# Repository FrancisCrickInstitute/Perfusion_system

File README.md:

# Perfusion_system

This system is composed by a 3D printed lid for 35 mm petri dishes, two peristaltic pumps and a control board which controls the flow rate of both pumps simultaneously.

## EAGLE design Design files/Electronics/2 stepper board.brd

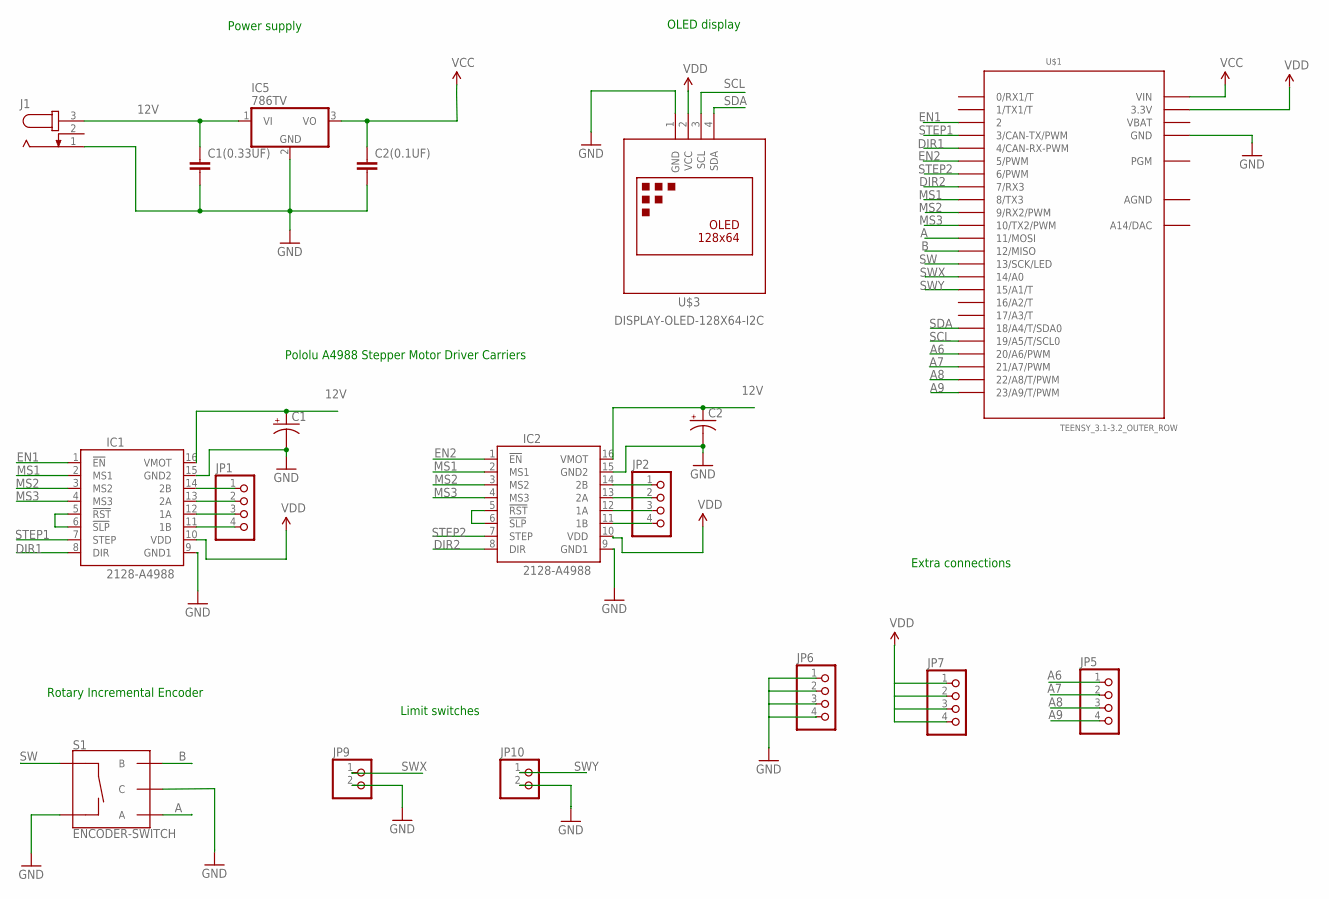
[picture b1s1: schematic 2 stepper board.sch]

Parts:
C1, C2: CPOL-USE5-5; E5-5
C1(0.33UF): C2.5/4; C2.5-4
C2(0.1UF): C2.5/2; C2.5-2
IC1, IC2: 2128-A4988; A4988
IC5: 786TV; TO220V
J1: JACK-PLUG0; SPC4077
JP1, JP2, JP5, JP6, JP7: PINHD-1X4; 1X04
JP9, JP10: PINHD-1X2; 1X02
S1: ENCODER-SWITCH; ROTARY_ENC_PLAIN
U$1: TEENSY_3.1-3.2_OUTER_ROW; TEENSY_3.0-3.2&LC_OUTER_ROW
U$3: DISPLAY-OLED-128X64-I2C

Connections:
12V: C1.+, C1(0.33UF).1, C2.+, IC1.16 (VMOT), IC2.16 (VMOT), IC5.1 (VI), J1.3
A: S1.A, U$1.11 (11/MOSI)
A6: JP5.1, U$1.20/A6 (20/A6/PWM)
A7: JP5.2, U$1.21/A7 (21/A7/PWM)
A8: JP5.3, U$1.22/A8 (22/A8/T/PWM)
A9: JP5.4, U$1.23/A9 (23/A9/T/PWM)
AGND: U$1.AGND
B: S1.B, U$1.12 (12/MISO)
DIR1: IC1.8 (DIR), U$1.4 (4/CAN-RX-PWM)
DIR2: IC2.8 (DIR), U$1.7 (7/RX3)
EN1: IC1.1 (!EN), U$1.2
EN2: IC2.1 (!EN), U$1.5 (5/PWM)
GND: C1.-, C1(0.33UF).2, C2.-, C2(0.1UF).2, IC1.9 (GND1), IC1.15 (GND2), IC2.9 (GND1), IC2.15 (GND2), IC5.2 (GND), J1.1, JP6.1, JP6.2, JP6.3, JP6.4, JP9.2, JP10.2, S1.C, S1.SW-, U$1.GND, U$1.GND1 (GND), U$3.1 (GND)
MS1: IC1.2 (MS1), IC2.2 (MS1), U$1.8 (8/TX3)
MS2: IC1.3 (MS2), IC2.3 (MS2), U$1.9 (9/RX2/PWM)
MS3: IC1.4 (MS3), IC2.4 (MS3), U$1.10 (10/TX2/PWM)
unnamed: IC1.14 (2B), JP1.1
unnamed: IC1.13 (2A), JP1.2
unnamed: IC1.12 (1A), JP1.3
unnamed: IC1.11 (1B), JP1.4
unnamed: IC2.14 (2B), JP2.1
unnamed: IC2.13 (2A), JP2.2
unnamed: IC2.12 (1A), JP2.3
unnamed: IC2.11 (1B), JP2.4
unnamed: IC2.5 (!RST), IC2.6 (!SLP)
unnamed: IC1.5 (!RST), IC1.6 (!SLP)
SCL: U$1.19/A5 (19/A5/T/SCL0), U$3.3 (SCL)
SDA: U$1.18/A4 (18/A4/T/SDA0), U$3.4 (SDA)
STEP1: IC1.7 (STEP), U$1.3 (3/CAN-TX/PWM)
STEP2: IC2.7 (STEP), U$1.6 (6/PWM)
SW: S1.SW+, U$1.13 (13/SCK/LED)
SWX: JP9.1, U$1.14/A0
SWY: JP10.1, U$1.15/A1 (15/A1/T)
VBAT: U$1.VBAT
VCC: C2(0.1UF).1, IC5.3 (VO), U$1.VIN
VDD: IC1.10 (VDD), IC2.10 (VDD), JP7.1, JP7.2, JP7.3, JP7.4, U$1.3.3V, U$1.3.3V1 (3.3V), U$3.2 (VCC)

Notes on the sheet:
Pololu A4988 Stepper Motor Driver Carriers
OLED display
Power supply
Rotary Incremental Encoder
Extra connections
Limit switches

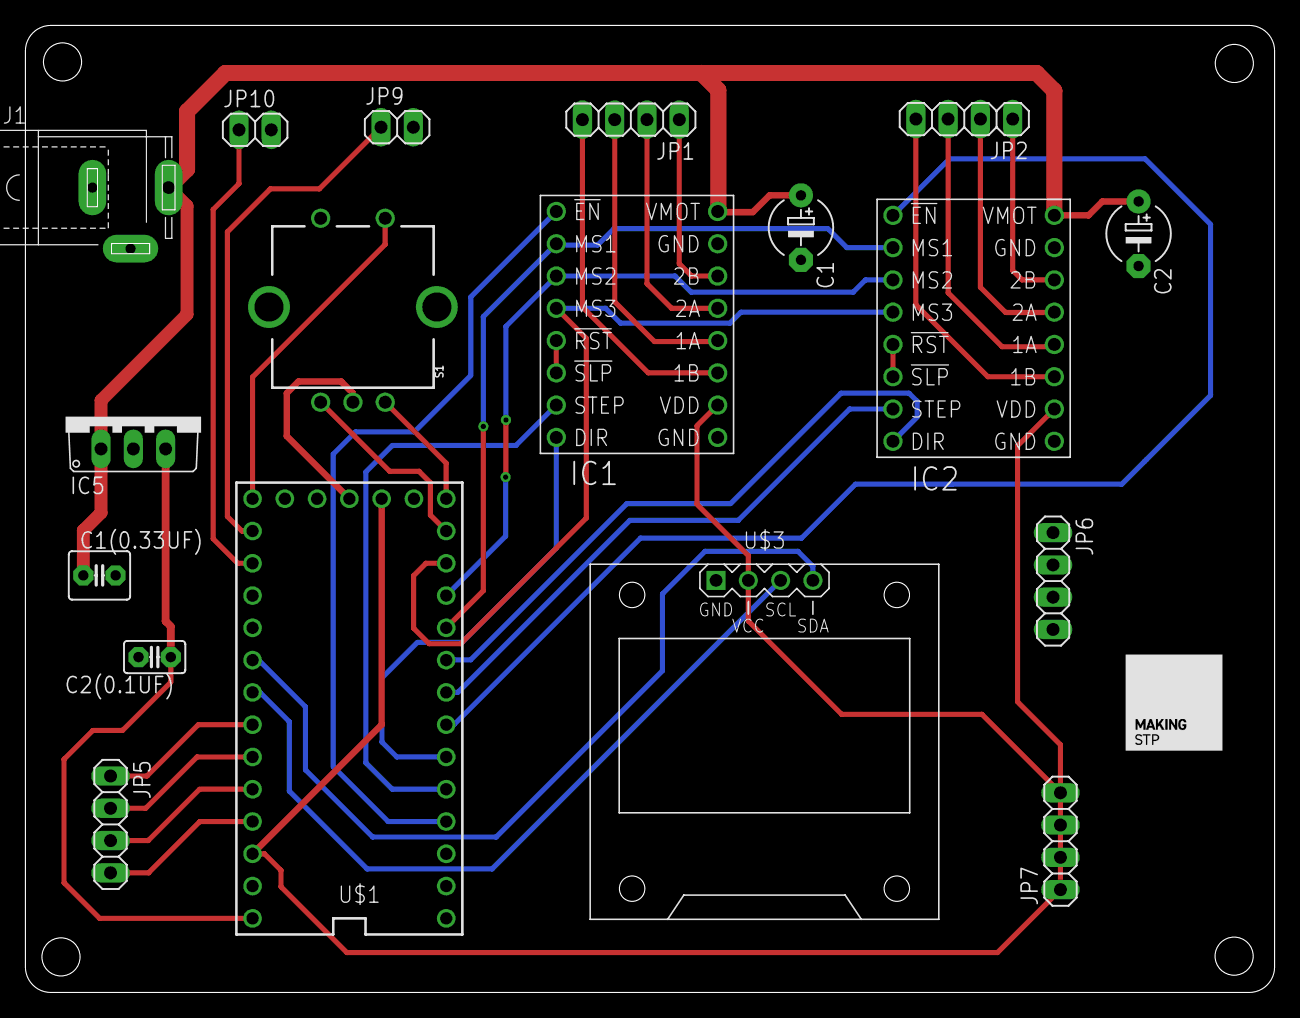
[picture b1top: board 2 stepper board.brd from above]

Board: 2 copper layers, 98.3 x 76.1 mm, 18 parts (0 on the bottom side), 34 nets.

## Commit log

2022-11-10 Firmware 2

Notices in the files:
parts and their libraries:
diy-modules: Released under the Creative Commons Attribution 4.0 International License: http://creativecommons.org/licenses/by/4.0
SparkFun-Switches: Licensing: Creative Commons ShareAlike 4.0 International - https://creativecommons.org/licenses/by-sa/4.0
